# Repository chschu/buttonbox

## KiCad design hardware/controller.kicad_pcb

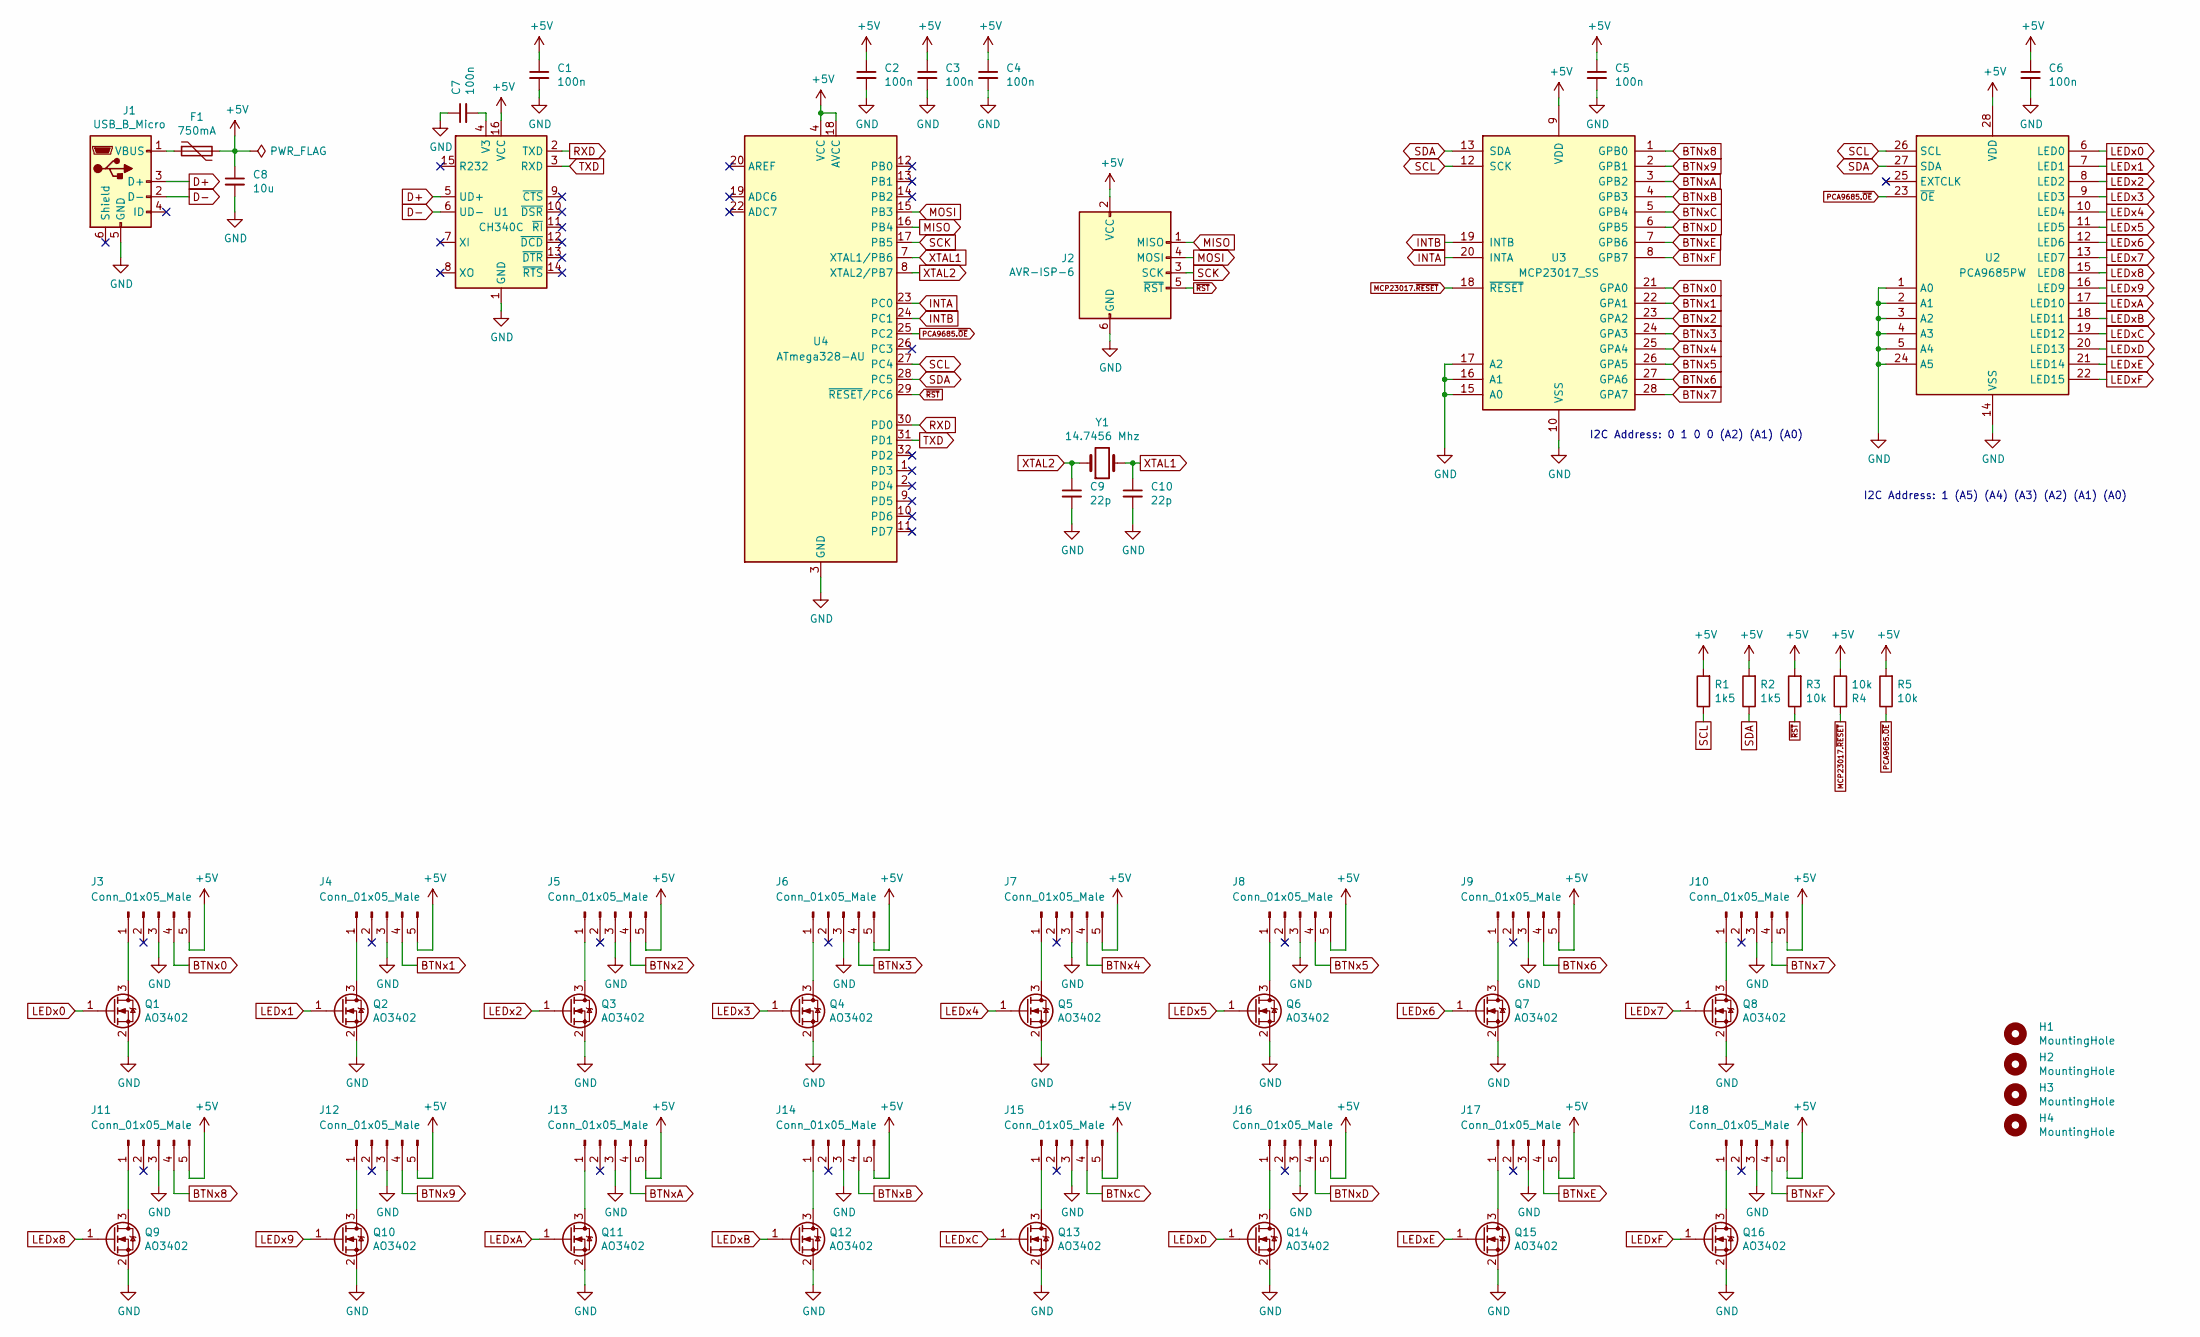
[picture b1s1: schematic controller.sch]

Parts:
C1, C2, C3, C4, C5, C6, C7: 100n; C_0805_2012Metric
C8: 10u; C_Disc_D6.0mm_W2.5mm_P5.00mm
C9, C10: 22p; C_0805_2012Metric
F1: 750mA; Fuse_0805_2012Metric
H1, H2, H3, H4: MountingHole; MountingHole_3.5mm
J1: USB_B_Micro; USB_Micro-B_Amphenol_10103594-0001LF_Horizontal
J2: AVR-ISP-6; PinHeader_2x03_P2.54mm_Vertical
J3, J4, J5, J6, J7, J8, J9, J10, J11, J12, J13, J14, J15, J16, J17, J18: Conn_01x05_Male; JST_XH_B5B-XH-A_1x05_P2.50mm_Vertical
Q1, Q2, Q3, Q4, Q5, Q6, Q7, Q8, Q9, Q10, Q11, Q12, Q13, Q14, Q15, Q16: AO3402; SOT-23
R1, R2: 1k5; R_0805_2012Metric
R3, R4, R5: 10k; R_0805_2012Metric
U1: CH340C; SOIC-16_3.9x9.9mm_P1.27mm
U2: PCA9685PW; TSSOP-28_4.4x9.7mm_P0.65mm
U3: MCP23017_SS; SSOP-28_5.3x10.2mm_P0.65mm
U4: ATmega328-AU; TQFP-32_7x7mm_P0.8mm
Y1: 14.7456 Mhz; Crystal_SMD_HC49-SD

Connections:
+5V: C1.1, C2.1, C3.1, C4.1, C5.1, C6.1, C8.1, F1.2, J2.2 (VCC), J3.5, J4.5, J5.5, J6.5, J7.5, J8.5, J9.5, J10.5, J11.5, J12.5, J13.5, J14.5, J15.5, J16.5, J17.5, J18.5, R1.2, R2.2, R3.2, R4.1, R5.2, U1.16 (VCC), U2.28 (VDD), U3.9 (VDD), U4.4 (VCC), U4.6 (VCC), U4.18 (AVCC)
BTNx0: J3.4, U3.21 (GPA0)
BTNx1: J4.4, U3.22 (GPA1)
BTNx2: J5.4, U3.23 (GPA2)
BTNx3: J6.4, U3.24 (GPA3)
BTNx4: J7.4, U3.25 (GPA4)
BTNx5: J8.4, U3.26 (GPA5)
BTNx6: J9.4, U3.27 (GPA6)
BTNx7: J10.4, U3.28 (GPA7)
BTNx8: J11.4, U3.1 (GPB0)
BTNx9: J12.4, U3.2 (GPB1)
BTNxA: J13.4, U3.3 (GPB2)
BTNxB: J14.4, U3.4 (GPB3)
BTNxC: J15.4, U3.5 (GPB4)
BTNxD: J16.4, U3.6 (GPB5)
BTNxE: J17.4, U3.7 (GPB6)
BTNxF: J18.4, U3.8 (GPB7)
D+: J1.3 (D+), U1.5 (UD+)
D-: J1.2 (D-), U1.6 (UD-)
GND: C1.2, C2.2, C3.2, C4.2, C5.2, C6.2, C7.1, C8.2, C9.2, C10.2, J1.5 (GND), J2.6 (GND), J3.3, J4.3, J5.3, J6.3, J7.3, J8.3, J9.3, J10.3, J11.3, J12.3, J13.3, J14.3, J15.3, J16.3, J17.3, J18.3, Q1.2 (S), Q2.2 (S), Q3.2 (S), Q4.2 (S), Q5.2 (S), Q6.2 (S), Q7.2 (S), Q8.2 (S), Q9.2 (S), Q10.2 (S), Q11.2 (S), Q12.2 (S), Q13.2 (S), Q14.2 (S), Q15.2 (S), Q16.2 (S), U1.1 (GND), U2.1 (A0), U2.2 (A1), U2.3 (A2), U2.4 (A3), U2.5 (A4), U2.14 (VSS), U2.24 (A5), U3.10 (VSS), U3.15 (A0), U3.16 (A1), U3.17 (A2), U4.3 (GND), U4.5 (GND), U4.21 (GND)
INTA: U3.20 (INTA), U4.23 (PC0)
INTB: U3.19 (INTB), U4.24 (PC1)
LEDx0: Q1.1 (G), U2.6 (LED0)
LEDx1: Q2.1 (G), U2.7 (LED1)
LEDx2: Q3.1 (G), U2.8 (LED2)
LEDx3: Q4.1 (G), U2.9 (LED3)
LEDx4: Q5.1 (G), U2.10 (LED4)
LEDx5: Q6.1 (G), U2.11 (LED5)
LEDx6: Q7.1 (G), U2.12 (LED6)
LEDx7: Q8.1 (G), U2.13 (LED7)
LEDx8: Q9.1 (G), U2.15 (LED8)
LEDx9: Q10.1 (G), U2.16 (LED9)
LEDxA: Q11.1 (G), U2.17 (LED10)
LEDxB: Q12.1 (G), U2.18 (LED11)
LEDxC: Q13.1 (G), U2.19 (LED12)
LEDxD: Q14.1 (G), U2.20 (LED13)
LEDxE: Q15.1 (G), U2.21 (LED14)
LEDxF: Q16.1 (G), U2.22 (LED15)
MCP23017.~RESET: R4.2, U3.18 (~RESET~)
MISO: J2.1 (MISO), U4.16 (PB4)
MOSI: J2.4 (MOSI), U4.15 (PB3)
unnamed: C7.2, U1.4 (V3)
unnamed: F1.1, J1.1 (VBUS)
unnamed: J3.1, Q1.3 (D)
unnamed: J4.1, Q2.3 (D)
unnamed: J5.1, Q3.3 (D)
unnamed: J6.1, Q4.3 (D)
unnamed: J7.1, Q5.3 (D)
unnamed: J8.1, Q6.3 (D)
unnamed: J9.1, Q7.3 (D)
unnamed: J10.1, Q8.3 (D)
unnamed: J11.1, Q9.3 (D)
unnamed: J12.1, Q10.3 (D)
unnamed: J13.1, Q11.3 (D)
unnamed: J14.1, Q12.3 (D)
unnamed: J15.1, Q13.3 (D)
unnamed: J16.1, Q14.3 (D)
unnamed: J17.1, Q15.3 (D)
unnamed: J18.1, Q16.3 (D)
PCA9685.~OE: R5.1, U2.23 (~OE), U4.25 (PC2)
RXD: U1.2 (TXD), U4.30 (PD0)
SCK: J2.3 (SCK), U4.17 (PB5)
SCL: R1.1, U2.26 (SCL), U3.12 (SCK), U4.27 (PC4)
SDA: R2.1, U2.27 (SDA), U3.13 (SDA), U4.28 (PC5)
TXD: U1.3 (RXD), U4.31 (PD1)
XTAL1: C10.1, U4.7 (XTAL1/PB6), Y1.2
XTAL2: C9.1, U4.8 (XTAL2/PB7), Y1.1
~RST: J2.5 (~RST), R3.1, U4.29 (~RESET~/PC6)

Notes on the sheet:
I2C Address: 1 (A5) (A4) (A3) (A2) (A1) (A0)
I2C Address: 0 1 0 0 (A2) (A1) (A0)

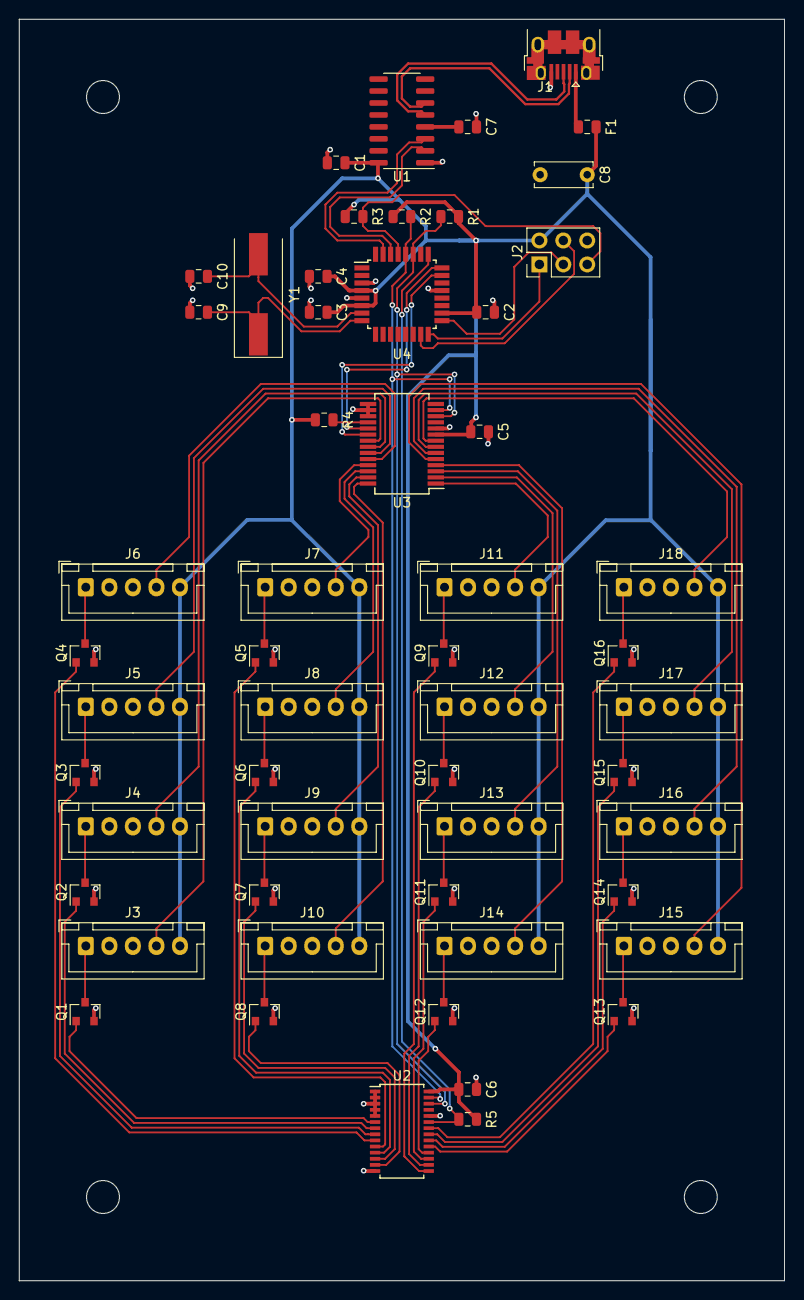
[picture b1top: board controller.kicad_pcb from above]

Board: 2 copper layers, 81.3 x 134.0 mm, 59 parts (0 on the bottom side), 68 nets.

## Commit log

2020-02-04 add schematic
2020-02-07 rename files, update library references
2020-02-07 move .gitignore entries to subdirectory
2020-02-10 connect buttons' NO to GND (MCP23017 has configurable internal pull-up resistors)
2020-02-10 small schematic layout fixes
2020-02-10 add howto for via stitching
2020-02-13 add simple controller software
2020-02-13 implement own cycle-based timeout
2020-02-13 set CPU frequency to 160 MHz
2020-03-26 switch to ESP32, implement timerless blinker
2020-03-26 read all bytes available from Serial at once
2020-04-07 switch to ATmega8, use shorter serial protocol, add PCA9685 stuff, use MCP23017 for buttons (not debounced yet)
2020-04-08 add debouncer, use pointers instead of copies for large-ish objects, use static initialization instead of new
2020-04-08 use templates for fractional gamma
2020-04-13 simplify initialization animation, change fuses to reduce start-up time
2020-04-14 use ATmega8, add PCB (before automatic rounting)
2020-08-22 update schematic with separate connectors for LEDs and buttons
2020-08-22 change Blinker to make it stoppable at arbitrary phases, use phase 0.9 for 'off'
2020-08-22 fix pull-up resistors: MCP23017.~RESET is always pulled high; PCA9685.~OE is pulled high but can be driven low by PC2
2020-08-22 fix assignment of SCL and SDA pins on ATmega328p
2020-08-22 disable brown-out detection
2020-08-22 combine similar code, use modff instead of fmodf
2020-08-22 increase I2C clock frequency
2020-08-22 use macOS CH340 driver
2020-08-22 fix capitalization of board
2020-08-22 combine Blinker::_next_on and Blinker::_next_of into a single byte
2020-08-22 update platform and libraries
2020-08-22 implement own Debouncer without Arduino dependency; avoid using millis() to save space
2020-08-22 render only if phase changed
2020-08-22 change comment for chip erase
2020-08-22 use correct bit constants (same value)
2020-08-22 configure build for ATmega328p
2020-08-22 implement binary serial protocol
2020-08-22 use gamma of 2.75
2020-08-22 use board_hardware.* settings to define fuses
2020-08-22 export Gerber and Drill files
2020-08-22 use 36pF capacitors for crystal
2020-08-22 initialize EEPROM with all 255 (no connectors mapped); enter config mode if no connectors are mapped yet
2020-08-22 remove test points
2020-08-22 add configurable and persistent mappings between physical connector number and logical value to support reduced number of connectors
2020-08-22 manually define fuses because low power oscillator seems to be more stable when touching the board
2020-08-22 add render call to Blinker::attach(), remove unused code
2020-08-22 change USB connector, finalize PCB shape
2020-08-22 create routing-friendly PCB layout and route it manually
2020-08-22 read all inputs of MCP23017 at once
2020-08-22 simplify serial protocol
2020-08-22 combine nested conditions into one
2020-08-22 drive PC2 low to enable PCA9685 outputs after initialization
2020-08-22 clear EEPROM when entering config mode, update each mapping as a single byte
2020-08-22 fix polyfuse rating
2020-08-22 use specific bit constants
2020-08-22 iterate over mapped connectors only
2020-08-22 skip initialization of Serial in config mode
2020-08-29 reset I2C bus at startup to reset stuck PCA9685 during development
2020-08-30 use AVR TWI to control PCA9685 and MCP23017 (smaller binary)
2020-08-30 use AVR UART for serial communication (smaller binary)
2020-08-30 increase SCL clock to 800 kHz
2020-08-31 use naming 'ticks' in debouncer and blinker, consistently pass microseconds
2020-08-31 remove Arduino, use AVR Timer0 for timing
2020-08-31 group together initialization and loop for config mode
2020-09-01 use 16 bit timer (Timer1) to reduce number of interrupts
2020-09-01 fix non-monotonous cycle count caused by unhandled overflows
2020-09-01 use _BV macro for bit positions
2020-09-02 use leading underscore for #define in include files
2020-09-03 restore interrupt flag as soon as possible
2020-09-05 implement bootloader (based on AppNote AVR109) for serial programming
2020-09-06 add linker flag --relax to reduce binary size
2020-09-06 wait for completion of previous flash erase/write (SPM) befor reading flash or jumping to application
2020-09-06 change fuses to match smaller bootloader size, use verbose syntax to specify start of .text section
2020-09-06 add required nop between write to PORTB and read from PINB
2020-09-06 introduce union type to reduce code required for low and high byte access
2020-09-06 use linker symbol for jump/call to application
2020-09-06 wait for completion of EEPROM writes
2020-09-06 add second nop between write to PORTB and read from PIN
2020-09-06 perform cleanup before jumping to aplication
2020-11-05 use actual signature constants of target chip
